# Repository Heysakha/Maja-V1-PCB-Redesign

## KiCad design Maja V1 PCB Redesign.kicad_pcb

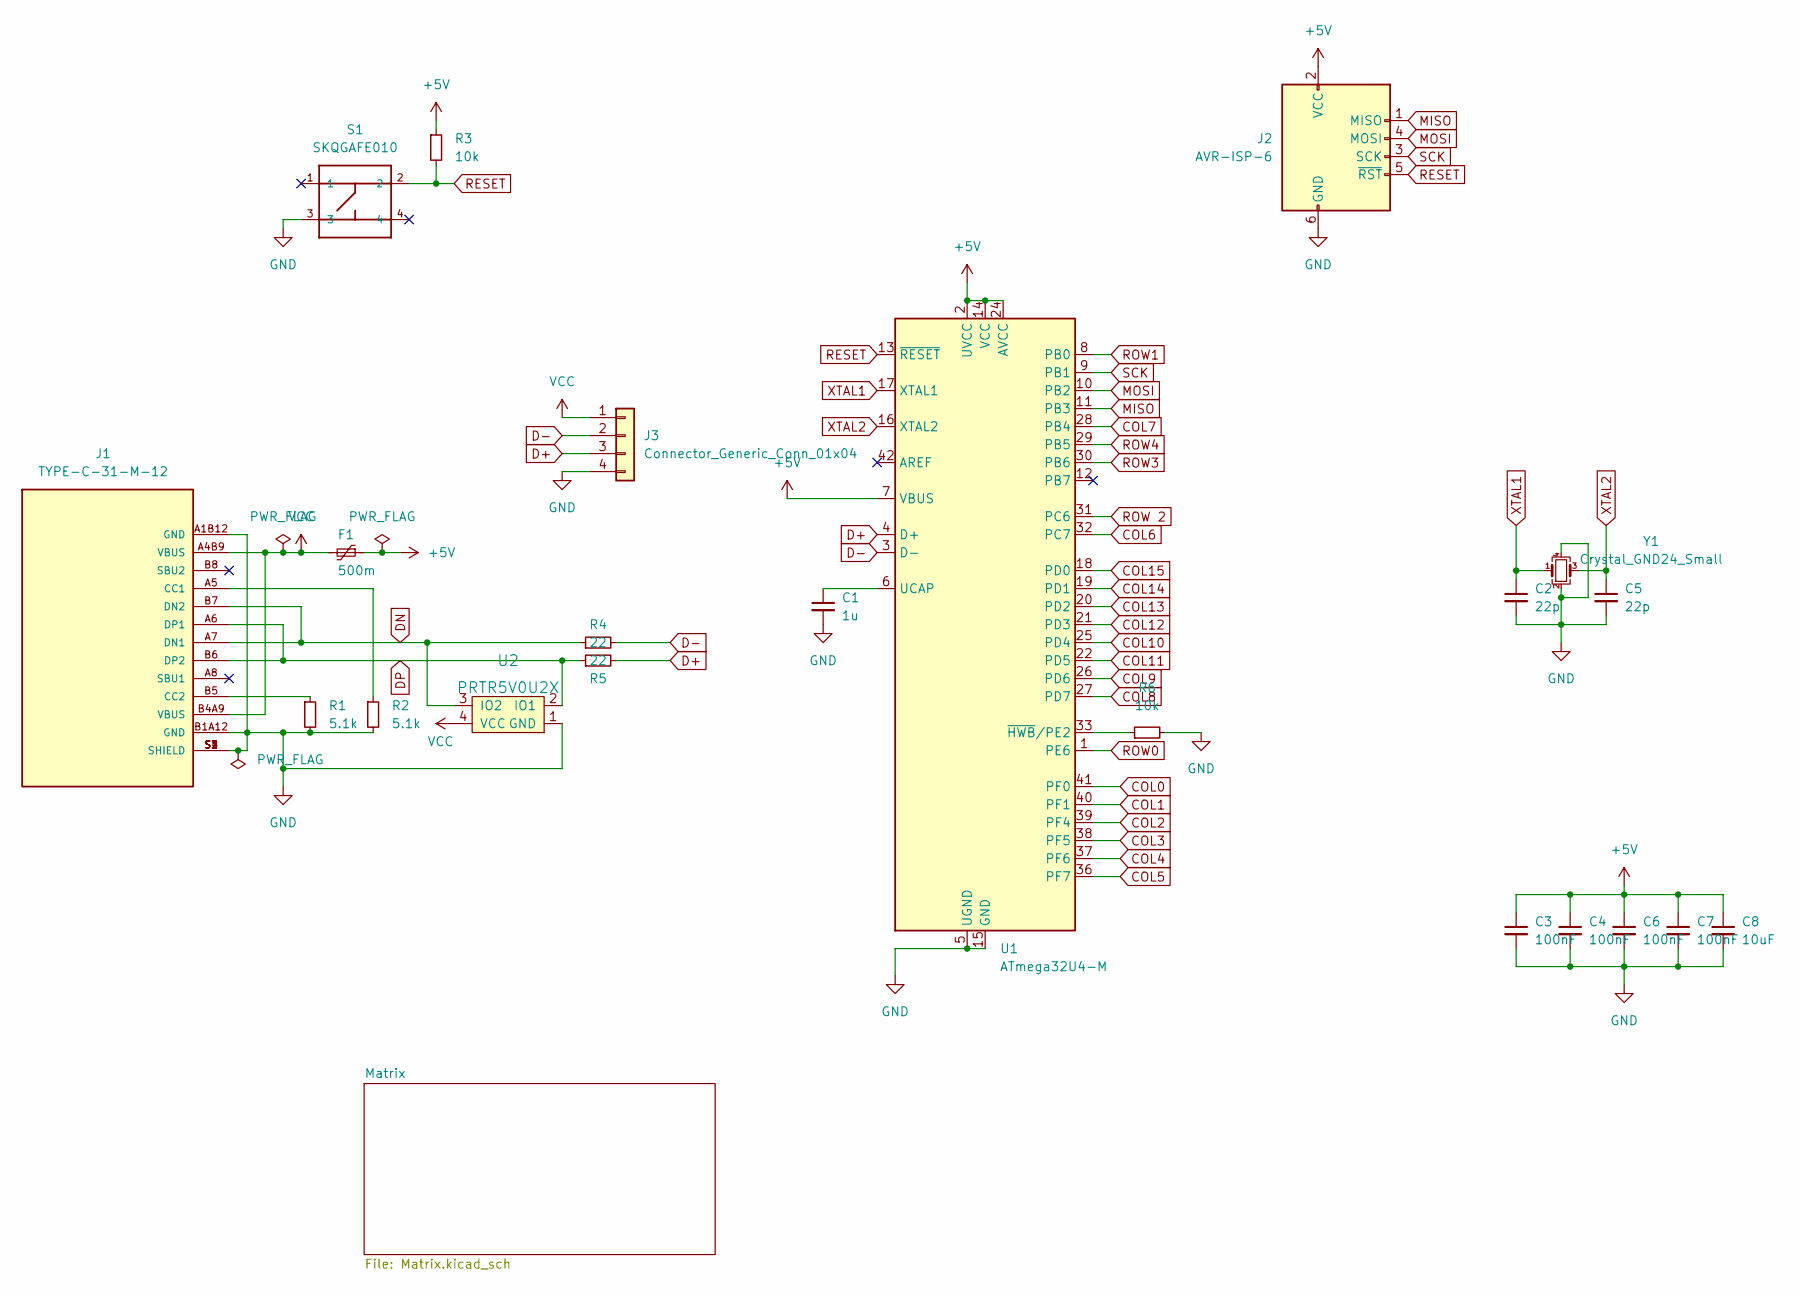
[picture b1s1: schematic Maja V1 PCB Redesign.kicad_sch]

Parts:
C1: 1u; C_0805_2012Metric_Pad1.18x1.45mm_HandSolder
C2, C5: 22p; C_0805_2012Metric_Pad1.18x1.45mm_HandSolder
C3, C4, C6, C7: 100nF; C_0805_2012Metric_Pad1.18x1.45mm_HandSolder
C8: 10uF; C_0805_2012Metric_Pad1.18x1.45mm_HandSolder
F1: 500m; Fuse_1206_3216Metric_Pad1.42x1.75mm_HandSolder
J1: TYPE-C-31-M-12; HRO_TYPE-C-31-M-12; PARTREV A
J2: AVR-ISP-6; Reset_Pretty
J3: Connector_Generic_Conn_01x04; JST_SH_SM04B-SRSS-TB_1x04-1MP_P1.00mm_Horizontal
R1, R2: 5.1k; R_0805_2012Metric_Pad1.20x1.40mm_HandSolder
R3, R6: 10k; R_0805_2012Metric_Pad1.20x1.40mm_HandSolder
R4, R5: 22; R_0805_2012Metric_Pad1.20x1.40mm_HandSolder
S1: SKQGAFE010; SW_SKQGAFE010; PART_REV B1
U1: ATmega32U4-M; QFN-44-1EP_7x7mm_P0.5mm_EP5.2x5.2mm
U2: PRTR5V0U2X; SOT143B
Y1: Crystal_GND24_Small; Crystal_SMD_3225-4Pin_3.2x2.5mm

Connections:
+5V: C3.1, C4.1, C6.1, C7.1, C8.1, F1.1, J2.2 (VCC), R3.1, U1.2 (UVCC), U1.7 (VBUS), U1.14 (VCC), U1.24 (AVCC), U1.34 (VCC), U1.44 (AVCC)
COL0: U1.41 (PF0); also elsewhere on the board
COL1: U1.40 (PF1); also elsewhere on the board
COL2: U1.39 (PF4); also elsewhere on the board
COL3: U1.38 (PF5); also elsewhere on the board
COL4: U1.37 (PF6); also elsewhere on the board
COL5: U1.36 (PF7); also elsewhere on the board
COL6: U1.32 (PC7); also elsewhere on the board
COL7: U1.28 (PB4); also elsewhere on the board
COL8: U1.27 (PD7); also elsewhere on the board
COL9: U1.26 (PD6); also elsewhere on the board
COL10: U1.25 (PD4); also elsewhere on the board
COL11: U1.22 (PD5); also elsewhere on the board
COL12: U1.21 (PD3); also elsewhere on the board
COL13: U1.20 (PD2); also elsewhere on the board
COL14: U1.19 (PD1); also elsewhere on the board
COL15: U1.18 (PD0); also elsewhere on the board
D+: J3.3, R5.2, U1.4 (D+)
D-: J3.2, R4.2, U1.3 (D-)
DN: J1.A7 (DN1), J1.B7 (DN2), R4.1, U2.3 (IO2)
DP: J1.A6 (DP1), J1.B6 (DP2), R5.1, U2.2 (IO1)
GND: C1.2, C2.2, C3.2, C4.2, C5.2, C6.2, C7.2, C8.2, J1.A1B12 (GND), J1.B1A12 (GND), J1.S1 (SHIELD), J1.S2 (SHIELD), J1.S3 (SHIELD), J1.S4 (SHIELD), J2.6 (GND), J3.4, R1.2, R2.2, R6.2, S1.3, U1.5 (UGND), U1.15 (GND), U1.23 (GND), U1.35 (GND), U1.43 (GND), U1.45 (GND), U2.1 (GND), Y1.2, Y1.4
MISO: J2.1 (MISO), U1.11 (PB3)
MOSI: J2.4 (MOSI), U1.10 (PB2)
unnamed: C1.1, U1.6 (UCAP)
unnamed: J1.A5 (CC1), R2.1
unnamed: J1.B5 (CC2), R1.1
unnamed: R6.1, U1.33 (~HWB/PE2)
RESET: J2.5 (~RST), R3.2, S1.2, U1.13 (~RESET)
ROW0: U1.1 (PE6); also elsewhere on the board
ROW1: U1.8 (PB0); also elsewhere on the board
ROW3: U1.30 (PB6); also elsewhere on the board
ROW4: U1.29 (PB5); also elsewhere on the board
ROW 2: U1.31 (PC6); also elsewhere on the board
SCK: J2.3 (SCK), U1.9 (PB1)
VCC: F1.2, J1.A4B9 (VBUS), J1.B4A9 (VBUS), J3.1, U2.4 (VCC)
XTAL1: C2.1, U1.17 (XTAL1), Y1.1
XTAL2: C5.1, U1.16 (XTAL2), Y1.3

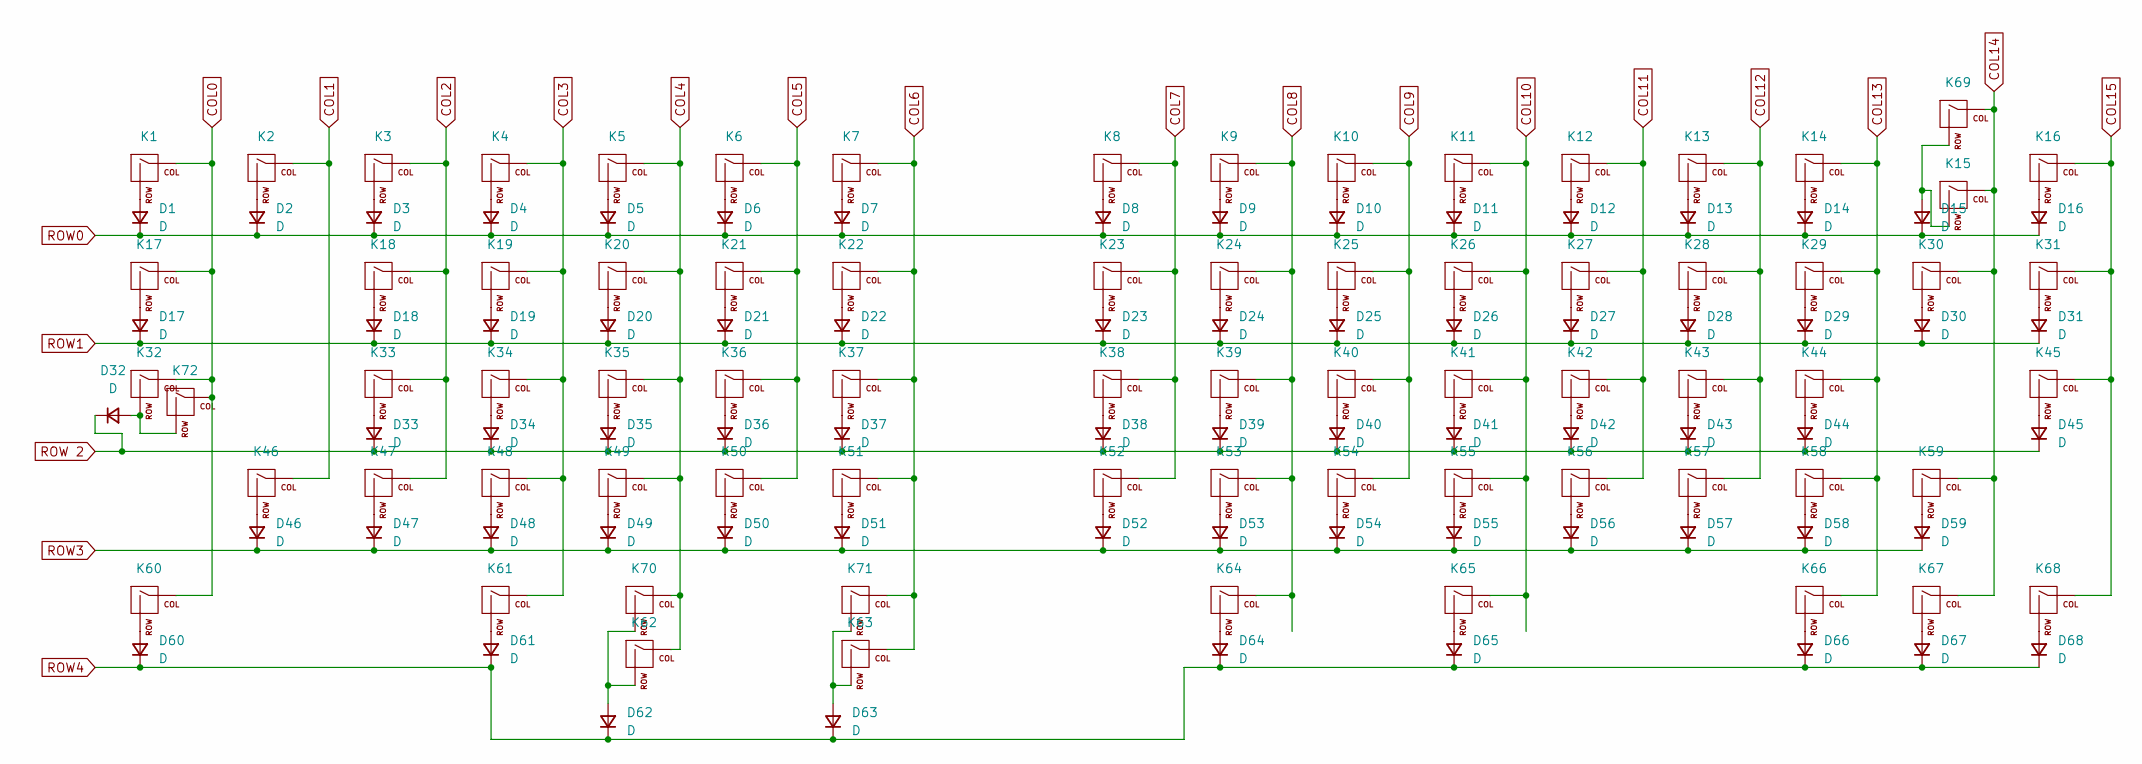
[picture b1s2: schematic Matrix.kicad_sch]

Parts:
D1, D2, D3, D4, D5, D6, D7, D8, D9, D10, D11, D12, D13, D14, D15, D16, D17, D18, D19, D20, D21, D22, D23, D24, D25, D26, D27, D28, D29, D30, D31, D32, D33, D34, D35, D36, D37, D38, D39, D40, D41, D42, D43, D44, D45, D46, D47, D48, D49, D50, D51, D52, D53, D54, D55, D56, D57, D58, D59, D60, D61, D62, D63, D64, D65, D66, D67, D68: D; D_SOD-123
K1: esc; SW_Cherry_MX_1.00u_PCB
K2: 1; SW_Cherry_MX_1.00u_PCB
K3: 2; SW_Cherry_MX_1.00u_PCB
K4: 3; SW_Cherry_MX_1.00u_PCB
K5: 4; SW_Cherry_MX_1.00u_PCB
K6: 5; SW_Cherry_MX_1.00u_PCB
K7: 6; SW_Cherry_MX_1.00u_PCB
K8: 7; SW_Cherry_MX_1.00u_PCB
K9: 8; SW_Cherry_MX_1.00u_PCB
K10: 9; SW_Cherry_MX_1.00u_PCB
K11: 0; SW_Cherry_MX_1.00u_PCB
K12: -; SW_Cherry_MX_1.00u_PCB
K13: =; SW_Cherry_MX_1.00u_PCB
K14: SW_Cherry_MX_1.00u_PCB
K15: split backspace; SW_Cherry_MX_1.00u_PCB
K16: macro1; SW_Cherry_MX_1.00u_PCB
K17: tab; SW_Cherry_MX_1.50u_PCB
K18: q; SW_Cherry_MX_1.00u_PCB
K19: w; SW_Cherry_MX_1.00u_PCB
K20: e; SW_Cherry_MX_1.00u_PCB
K21: r; SW_Cherry_MX_1.00u_PCB
K22: t; SW_Cherry_MX_1.00u_PCB
K23: y; SW_Cherry_MX_1.00u_PCB
K24: u; SW_Cherry_MX_1.00u_PCB
K25: i; SW_Cherry_MX_1.00u_PCB
K26: o; SW_Cherry_MX_1.00u_PCB
K27: p; SW_Cherry_MX_1.00u_PCB
K28: [; SW_Cherry_MX_1.00u_PCB
K29: ]; SW_Cherry_MX_1.00u_PCB
K30: \; SW_Cherry_MX_1.50u_PCB
K31: macro 2; SW_Cherry_MX_1.00u_PCB
K32: Caps; SW_Cherry_MX_1.75u_PCB
K33: a; SW_Cherry_MX_1.00u_PCB
K34: s; SW_Cherry_MX_1.00u_PCB
K35: d; SW_Cherry_MX_1.00u_PCB
K36: f; SW_Cherry_MX_1.00u_PCB
K37: g; SW_Cherry_MX_1.00u_PCB
K38: h; SW_Cherry_MX_1.00u_PCB
K39: j; SW_Cherry_MX_1.00u_PCB
K40: k; SW_Cherry_MX_1.00u_PCB
K41: l; SW_Cherry_MX_1.00u_PCB
K42: ;; SW_Cherry_MX_1.00u_PCB
K43: '; SW_Cherry_MX_1.00u_PCB
K44: enter; SW_Cherry_MX_2.25u_PCB
K45: macro 3; SW_Cherry_MX_1.00u_PCB
K46: shift; SW_Cherry_MX_2.25u_PCB
K47: z; SW_Cherry_MX_1.00u_PCB
K48: x; SW_Cherry_MX_1.00u_PCB
K49: c; SW_Cherry_MX_1.00u_PCB
K50: v; SW_Cherry_MX_1.00u_PCB
K51: b; SW_Cherry_MX_1.00u_PCB
K52: fn; SW_Cherry_MX_1.00u_PCB
K53: n; SW_Cherry_MX_1.00u_PCB
K54: m; SW_Cherry_MX_1.00u_PCB
K55: ,; SW_Cherry_MX_1.00u_PCB
K56: .; SW_Cherry_MX_1.00u_PCB
K57: /; SW_Cherry_MX_1.00u_PCB
K58: shift right; SW_Cherry_MX_1.75u_PCB
K59: up; SW_Cherry_MX_1.00u_PCB
K60: ctrl left; SW_Cherry_MX_1.50u_PCB
K61: alt right; SW_Cherry_MX_1.50u_PCB
K62: space left; SW_Cherry_MX_2.25u_PCB
K63: code; SW_Cherry_MX_1.00u_PCB
K64: space right; SW_Cherry_MX_2.75u_PCB
K65: ctrl right; SW_Cherry_MX_1.50u_PCB
K66: left; SW_Cherry_MX_1.00u_PCB
K67: down; SW_Cherry_MX_1.00u_PCB
K68: right; SW_Cherry_MX_1.00u_PCB
K69: backspace; SW_Cherry_MX_2.00u_PCB
K70: space left 2; SW_Cherry_MX_2.00u_PCB
K71: code 2; SW_Cherry_MX_1.25u_PCB
K72: Caps steped; SW_Cherry_MX_1.75u_PCB

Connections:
COL0: K1.1 (COL), K17.1 (COL), K32.1 (COL), K60.1 (COL), K72.1 (COL); also elsewhere on the board
COL1: K2.1 (COL), K46.1 (COL); also elsewhere on the board
COL2: K3.1 (COL), K18.1 (COL), K33.1 (COL), K47.1 (COL); also elsewhere on the board
COL3: K4.1 (COL), K19.1 (COL), K34.1 (COL), K48.1 (COL), K61.1 (COL); also elsewhere on the board
COL4: K5.1 (COL), K20.1 (COL), K35.1 (COL), K49.1 (COL), K62.1 (COL), K70.1 (COL); also elsewhere on the board
COL5: K6.1 (COL), K21.1 (COL), K36.1 (COL), K50.1 (COL); also elsewhere on the board
COL6: K7.1 (COL), K22.1 (COL), K37.1 (COL), K51.1 (COL), K63.1 (COL), K71.1 (COL); also elsewhere on the board
COL7: K8.1 (COL), K23.1 (COL), K38.1 (COL), K52.1 (COL); also elsewhere on the board
COL8: K9.1 (COL), K24.1 (COL), K39.1 (COL), K53.1 (COL), K64.1 (COL); also elsewhere on the board
COL9: K10.1 (COL), K25.1 (COL), K40.1 (COL), K54.1 (COL); also elsewhere on the board
COL10: K11.1 (COL), K26.1 (COL), K41.1 (COL), K55.1 (COL), K65.1 (COL); also elsewhere on the board
COL11: K12.1 (COL), K27.1 (COL), K42.1 (COL), K56.1 (COL); also elsewhere on the board
COL12: K13.1 (COL), K28.1 (COL), K43.1 (COL), K57.1 (COL); also elsewhere on the board
COL13: K14.1 (COL), K29.1 (COL), K44.1 (COL), K58.1 (COL), K66.1 (COL); also elsewhere on the board
COL14: K15.1 (COL), K30.1 (COL), K59.1 (COL), K67.1 (COL), K69.1 (COL); also elsewhere on the board
COL15: K16.1 (COL), K31.1 (COL), K45.1 (COL), K68.1 (COL); also elsewhere on the board
unnamed: D1.2 (A), K1.2 (ROW)
unnamed: D2.2 (A), K2.2 (ROW)
unnamed: D3.2 (A), K3.2 (ROW)
unnamed: D4.2 (A), K4.2 (ROW)
unnamed: D5.2 (A), K5.2 (ROW)
unnamed: D6.2 (A), K6.2 (ROW)
unnamed: D7.2 (A), K7.2 (ROW)
unnamed: D8.2 (A), K8.2 (ROW)
unnamed: D9.2 (A), K9.2 (ROW)
unnamed: D10.2 (A), K10.2 (ROW)
unnamed: D11.2 (A), K11.2 (ROW)
unnamed: D12.2 (A), K12.2 (ROW)
unnamed: D13.2 (A), K13.2 (ROW)
unnamed: D14.2 (A), K14.2 (ROW)
unnamed: D15.2 (A), K15.2 (ROW), K69.2 (ROW)
unnamed: D16.2 (A), K16.2 (ROW)
unnamed: D17.2 (A), K17.2 (ROW)
unnamed: D18.2 (A), K18.2 (ROW)
unnamed: D19.2 (A), K19.2 (ROW)
unnamed: D20.2 (A), K20.2 (ROW)
unnamed: D21.2 (A), K21.2 (ROW)
unnamed: D22.2 (A), K22.2 (ROW)
unnamed: D23.2 (A), K23.2 (ROW)
unnamed: D24.2 (A), K24.2 (ROW)
unnamed: D25.2 (A), K25.2 (ROW)
unnamed: D26.2 (A), K26.2 (ROW)
unnamed: D27.2 (A), K27.2 (ROW)
unnamed: D28.2 (A), K28.2 (ROW)
unnamed: D29.2 (A), K29.2 (ROW)
unnamed: D30.2 (A), K30.2 (ROW)
unnamed: D31.2 (A), K31.2 (ROW)
unnamed: D32.2 (A), K32.2 (ROW), K72.2 (ROW)
unnamed: D33.2 (A), K33.2 (ROW)
unnamed: D34.2 (A), K34.2 (ROW)
unnamed: D35.2 (A), K35.2 (ROW)
unnamed: D36.2 (A), K36.2 (ROW)
unnamed: D37.2 (A), K37.2 (ROW)
unnamed: D38.2 (A), K38.2 (ROW)
unnamed: D39.2 (A), K39.2 (ROW)
unnamed: D40.2 (A), K40.2 (ROW)
unnamed: D41.2 (A), K41.2 (ROW)
unnamed: D42.2 (A), K42.2 (ROW)
unnamed: D43.2 (A), K43.2 (ROW)
unnamed: D44.2 (A), K44.2 (ROW)
unnamed: D45.2 (A), K45.2 (ROW)
unnamed: D46.2 (A), K46.2 (ROW)
unnamed: D47.2 (A), K47.2 (ROW)
unnamed: D48.2 (A), K48.2 (ROW)
unnamed: D49.2 (A), K49.2 (ROW)
unnamed: D50.2 (A), K50.2 (ROW)
unnamed: D51.2 (A), K51.2 (ROW)
unnamed: D52.2 (A), K52.2 (ROW)
unnamed: D53.2 (A), K53.2 (ROW)
unnamed: D54.2 (A), K54.2 (ROW)
unnamed: D55.2 (A), K55.2 (ROW)
unnamed: D56.2 (A), K56.2 (ROW)
unnamed: D57.2 (A), K57.2 (ROW)
unnamed: D58.2 (A), K58.2 (ROW)
unnamed: D59.2 (A), K59.2 (ROW)
unnamed: D60.2 (A), K60.2 (ROW)
unnamed: D61.2 (A), K61.2 (ROW)
unnamed: D62.2 (A), K62.2 (ROW), K70.2 (ROW)
unnamed: D63.2 (A), K63.2 (ROW), K71.2 (ROW)
unnamed: D64.2 (A), K64.2 (ROW)
unnamed: D65.2 (A), K65.2 (ROW)
unnamed: D66.2 (A), K66.2 (ROW)
unnamed: D67.2 (A), K67.2 (ROW)
unnamed: D68.2 (A), K68.2 (ROW)
ROW0: D1.1 (K), D2.1 (K), D3.1 (K), D4.1 (K), D5.1 (K), D6.1 (K), D7.1 (K), D8.1 (K), D9.1 (K), D10.1 (K), D11.1 (K), D12.1 (K), D13.1 (K), D14.1 (K), D15.1 (K), D16.1 (K); also elsewhere on the board
ROW1: D17.1 (K), D18.1 (K), D19.1 (K), D20.1 (K), D21.1 (K), D22.1 (K), D23.1 (K), D24.1 (K), D25.1 (K), D26.1 (K), D27.1 (K), D28.1 (K), D29.1 (K), D30.1 (K), D31.1 (K); also elsewhere on the board
ROW3: D46.1 (K), D47.1 (K), D48.1 (K), D49.1 (K), D50.1 (K), D51.1 (K), D52.1 (K), D53.1 (K), D54.1 (K), D55.1 (K), D56.1 (K), D57.1 (K), D58.1 (K), D59.1 (K); also elsewhere on the board
ROW4: D60.1 (K), D61.1 (K), D62.1 (K), D63.1 (K), D64.1 (K), D65.1 (K), D66.1 (K), D67.1 (K), D68.1 (K); also elsewhere on the board
ROW 2: D32.1 (K), D33.1 (K), D34.1 (K), D35.1 (K), D36.1 (K), D37.1 (K), D38.1 (K), D39.1 (K), D40.1 (K), D41.1 (K), D42.1 (K), D43.1 (K), D44.1 (K), D45.1 (K); also elsewhere on the board

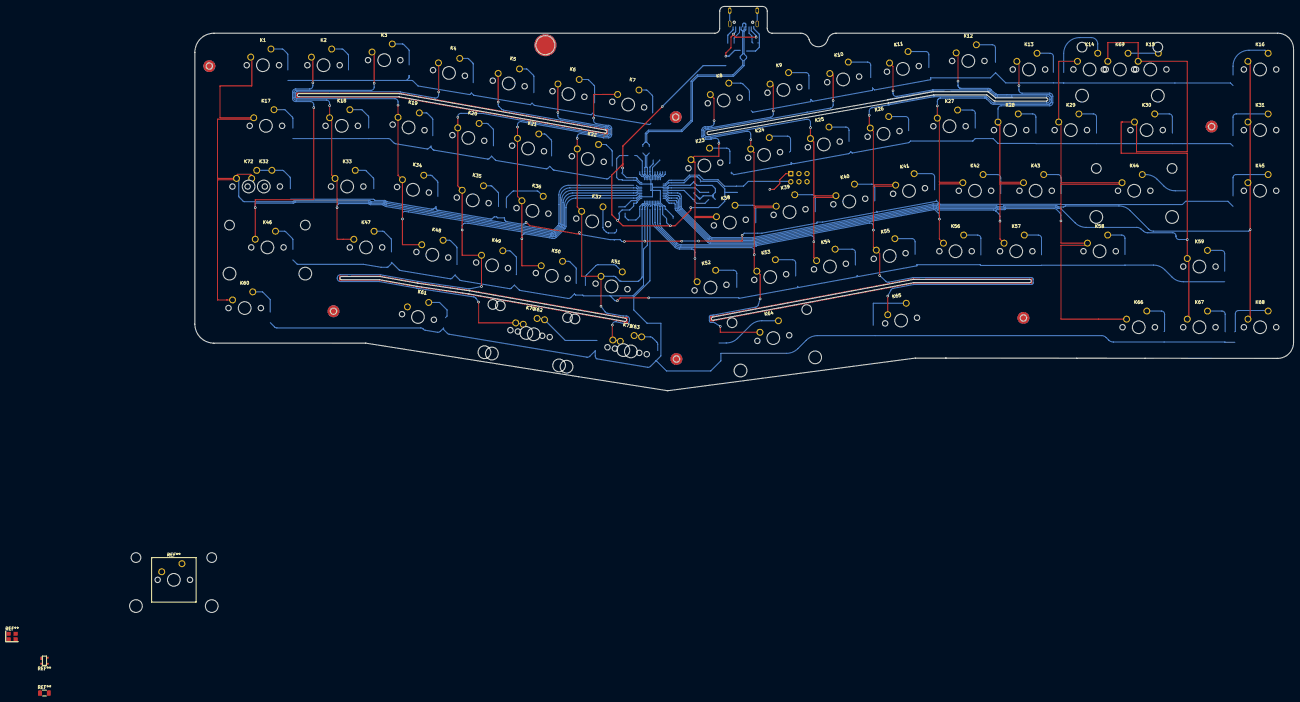
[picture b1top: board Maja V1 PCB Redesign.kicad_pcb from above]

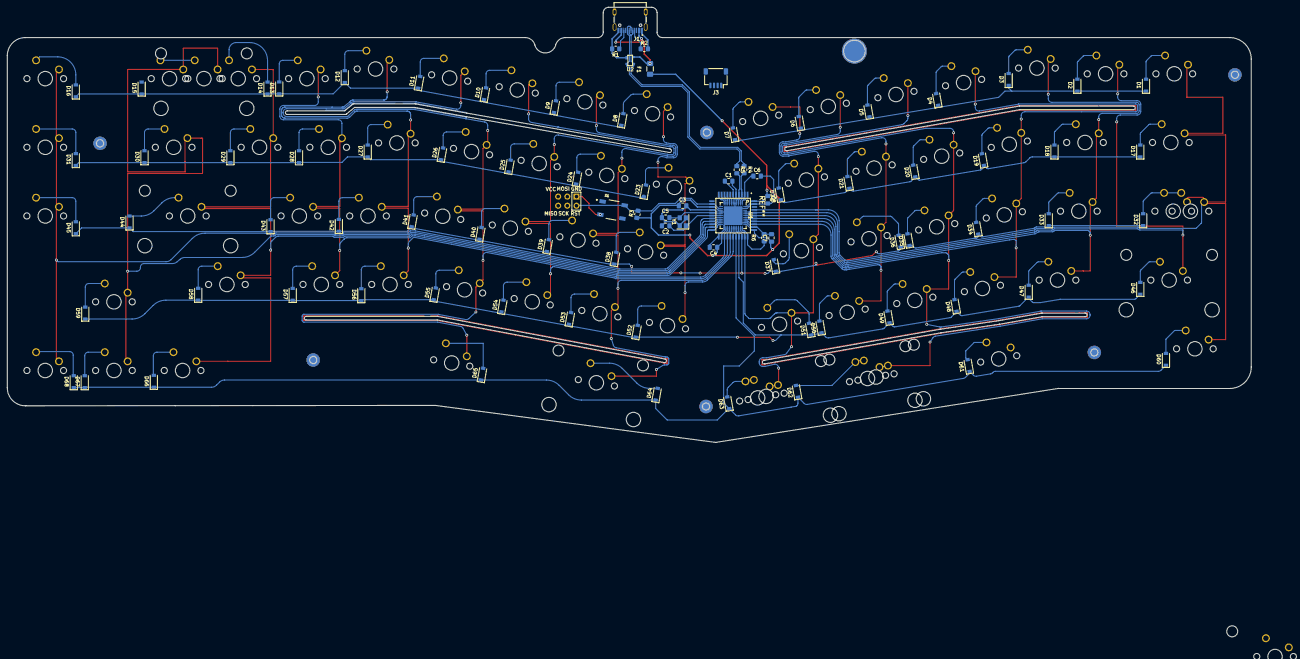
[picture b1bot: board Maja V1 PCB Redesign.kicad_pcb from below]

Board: 2 copper layers, 345.1 x 120.7 mm, 162 parts (90 on the bottom side), 106 nets.

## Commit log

2022-01-15 First
    Project Made
2022-01-15 Library Added
    Add library for component and footprint
2022-01-15 add footprint & library
2022-01-16 Add component
2022-01-18 Atmega Schematic
2022-01-20 Finish Wiring
    Schematic wiring
2022-01-21 fixed footprint & Symbol
2022-01-21 key placement
2022-01-21 add JST
2022-01-21 tracing 1
2022-01-22 routing 1
2022-01-22 routing 2
2022-01-23 finish col routing
2022-01-23 test silkscreen
2022-01-23 routing
2022-01-26 ROUTING DONE
2022-01-26 LCSC Component
2022-01-27 add farret
2022-01-27 revise copper fill
